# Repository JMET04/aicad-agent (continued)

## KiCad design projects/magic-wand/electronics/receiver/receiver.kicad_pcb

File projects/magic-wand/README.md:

# 魔法杖跨域工程原型包（Rev B）

> **CURRENT 2026-08-23:** Wand 配置保持冻结（几何/布线未变）；BOM 已补全 36/36 LCSC/C-number 并重建制造包，C_HAPTIC_REG/C_HAPTIC_VDD 以 Samsung CL05A105KP5NNNC/C14445 等效替代（X7R→X5R，已记录证据）。独立 receiver-effects 的八槽/八效果 host 逻辑已验证，A1 裸板候选已通过原生 ERC/DRC 并哈希绑定（旧 receiver CAM 仍为 **REJECTED**）。授权仅覆盖原型裸板与原型 3D 打印；PCBA、目标固件、HIL 和量产仍锁定，见 `integration/CURRENT_SYSTEM_STATUS.json`。

当前入口：

- [Current system status](integration/CURRENT_SYSTEM_STATUS.json) — 当前机器可读单一事实源；
- [System engineering handoff](integration/SYSTEM_ENGINEERING_HANDOFF.md) — 接口、开放门和插件升级经验；
- [冻结 Wand 嘉立创裸板包](electronics/manufacturing/jlcpcb-wand-rev-a0/) — 4 层、ERC/DRC 0 的 Wand 裸板上传候选；
- [可打印外壳包](mechanical/printable-wand/) — 含电池位、触觉位、STEP/STL、3D 预览和网格门禁；
- [receiver-effects 系统交接](integration/RECEIVER_EFFECTS_SYSTEM_HANDOFF.md) — 直接 BLE 端点、八槽/八效果、屏幕/音效和开放硬件门；
- [receiver-effects KiCad 工作源](electronics/receiver-effects/) — A1 60 × 50 mm、4 层；ERC/DRC 0/0/0，裸板上传候选已哈希绑定；
- [八类手势主机证据](firmware/gesture-host-evidence.json) — Wand 分类管线证据，不代替目标固件/HIL；
- [接收器运行时主机证据](firmware/host-review-evidence.json) — 34/34 build、10/10 CTest、cppcheck 9/9、52/52 哈希；目标/HIL 仍开放；
- [系统合同与 QA](integration/system-design-contract.json) — 跨域接口、证据和放行锁；
- [当前 SYS-001..012 追踪](integration/current-system-traceability.json) — Rev B 需求到当前合同、门禁和证据的机器映射；
- [当前交付哈希清单](integration/current-delivery-manifest.json) — 当前状态、合同、双交接和五项工具证据的精确闭包；
- [历史机械/电子/整合包](integration/README.md) — Rev A 追溯材料，不再是当前状态源；
- [整机审查 SVG](integration/system-review-overview.svg)；
- [成本粗算](integration/rough-cost-estimate.md)；
- [合并 BOM](integration/combined-bom.csv)。

在仓库根目录复核当前机械与系统门禁：

```powershell
python projects\magic-wand\mechanical\printable-wand\build_printable_wand.py
python plugins\aicad-agent\tests\test_system_engineering_contract.py -v
```

旧的 `integration/build_package.py` 只复现 Rev A 历史快照，不能生成当前状态。

Current authorization is limited to prototype bare-PCB fabrication and prototype 3D printing. The frozen Wand package is already a verified upload candidate; receiver-effects A1 is now also a verified bare-PCB upload candidate (ERC/DRC 0/0/0, hash-bound JLC archive; NINA In1 GND coverage 96% vs the 98% production target remains the only open manufacturing item). PCBA, target-firmware, HIL, production and safety-critical release locks remain closed.

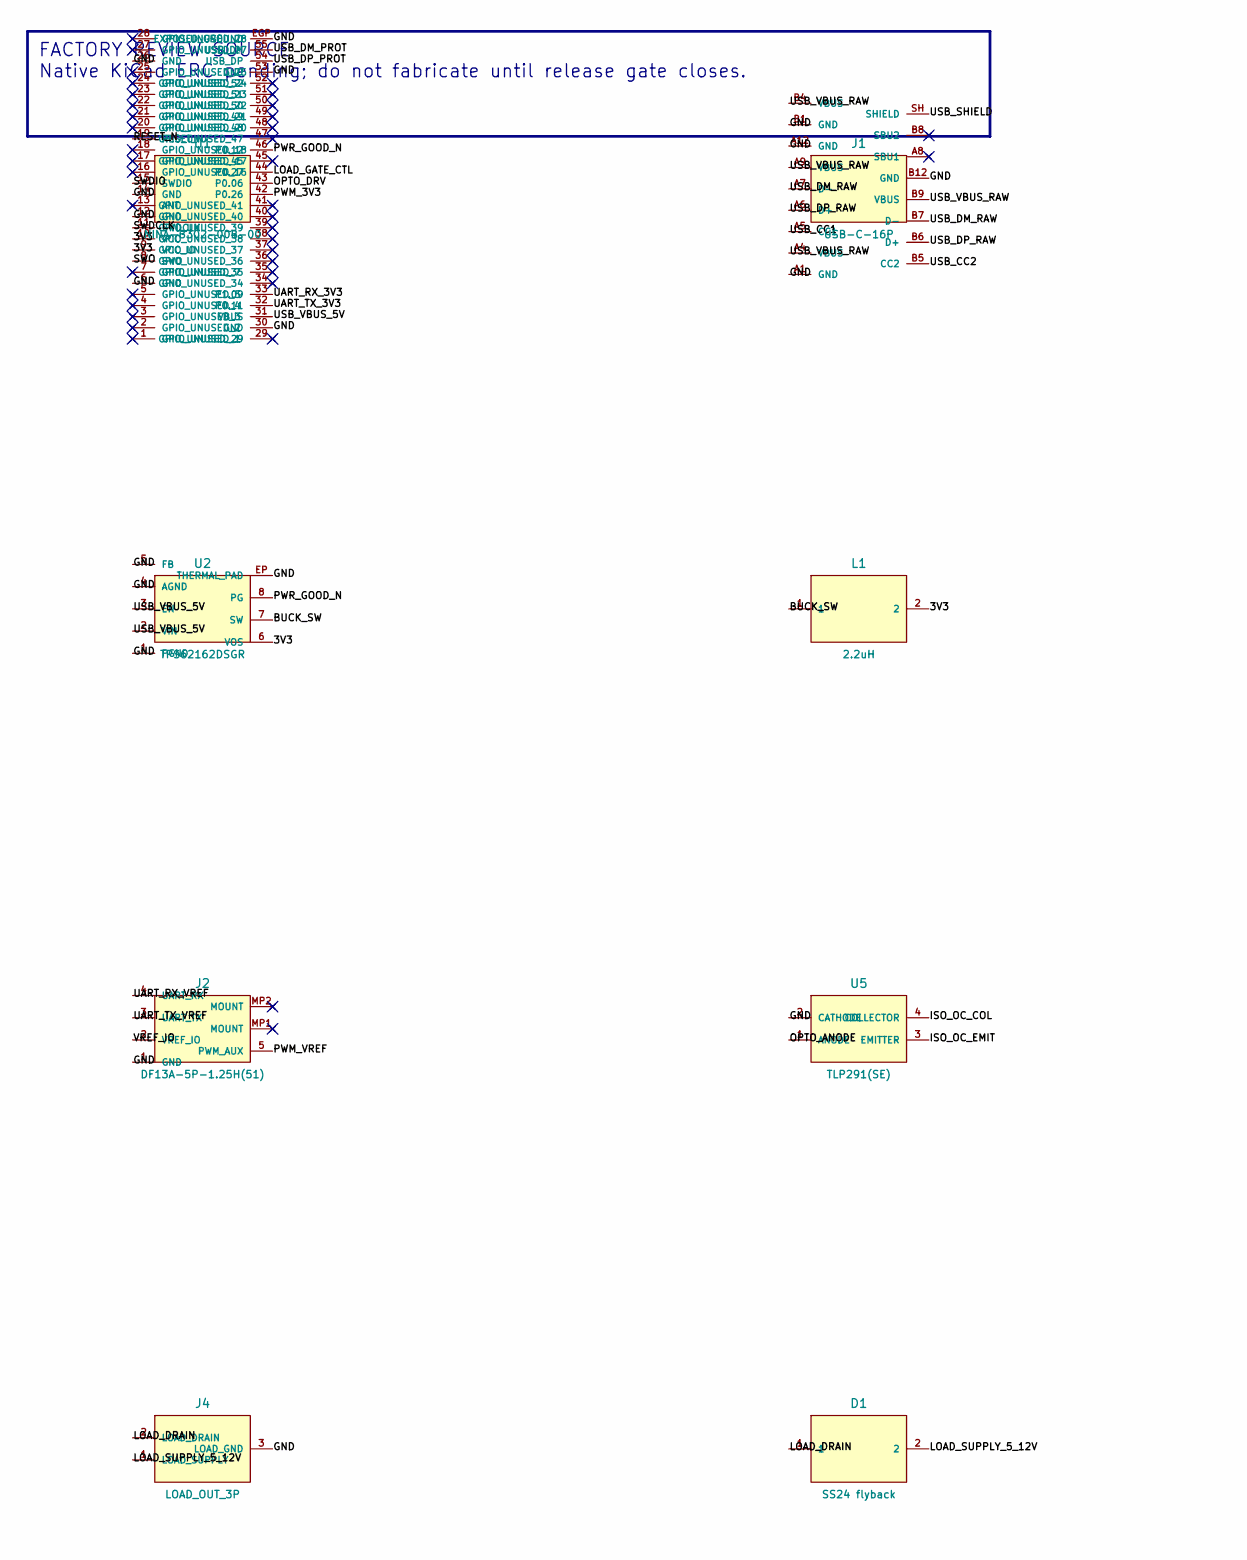
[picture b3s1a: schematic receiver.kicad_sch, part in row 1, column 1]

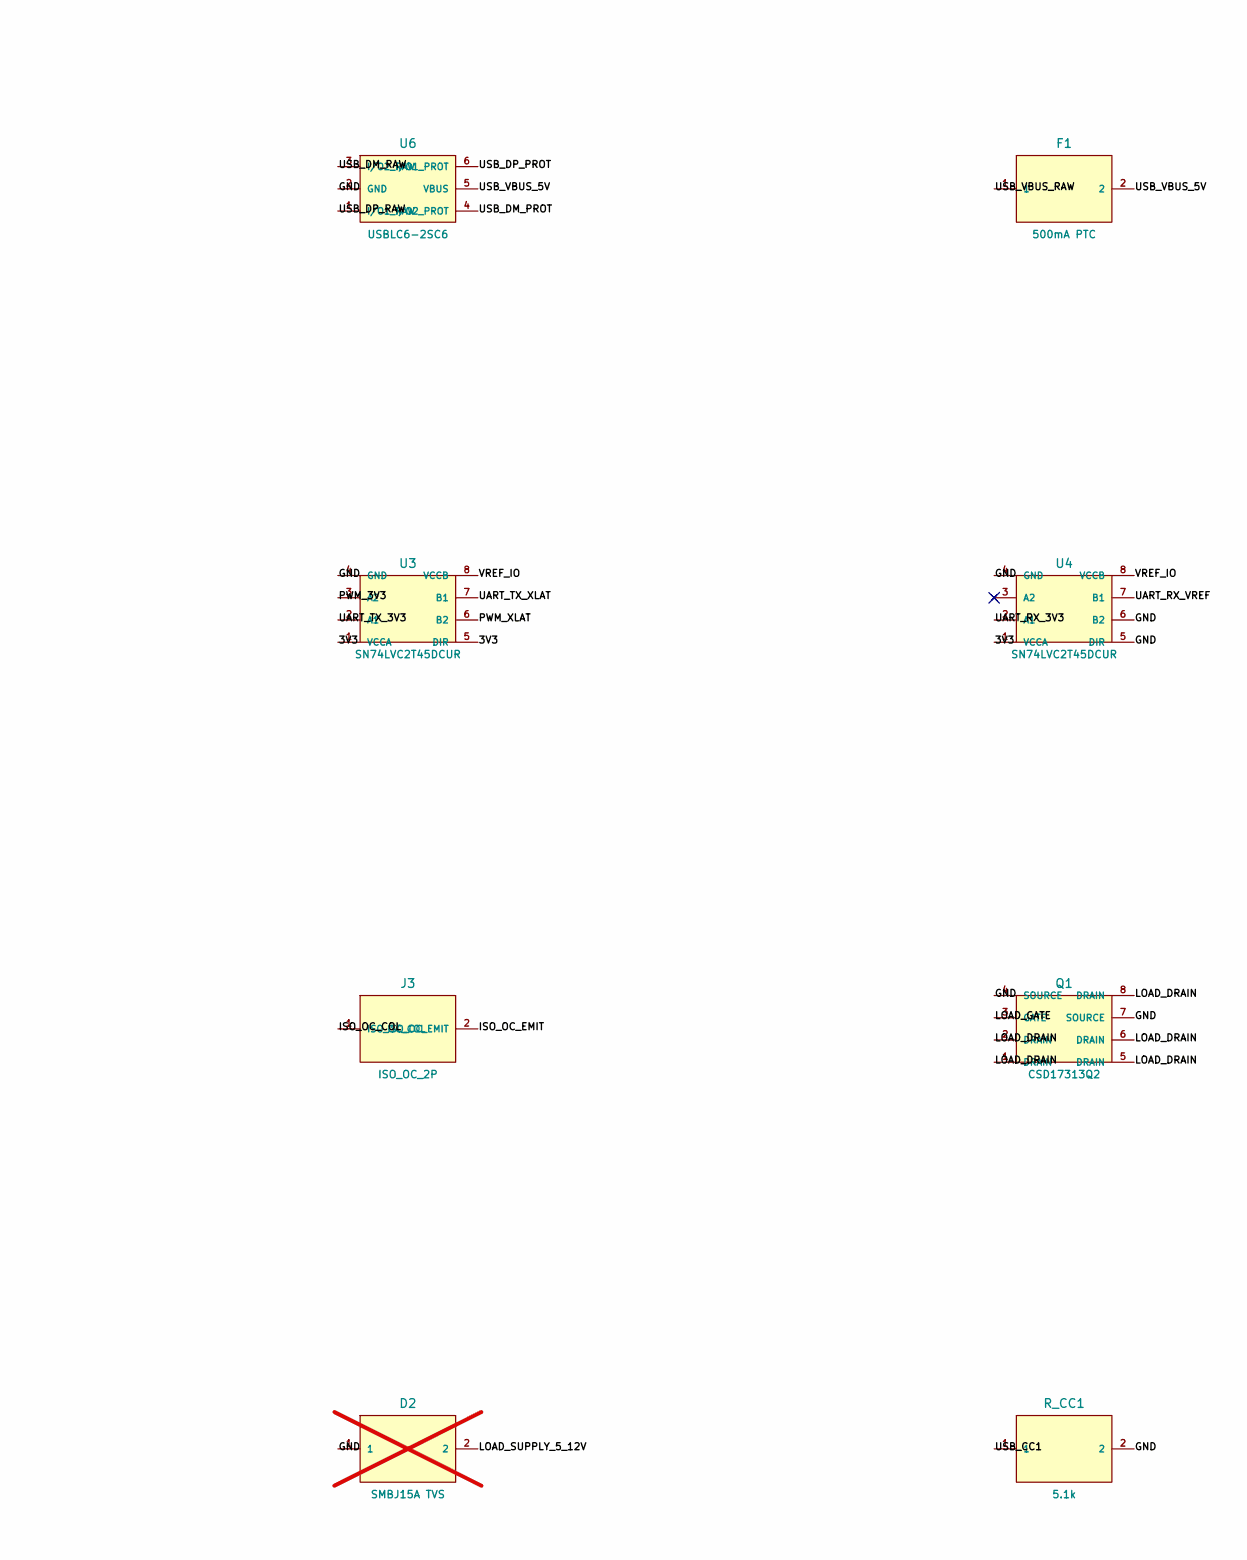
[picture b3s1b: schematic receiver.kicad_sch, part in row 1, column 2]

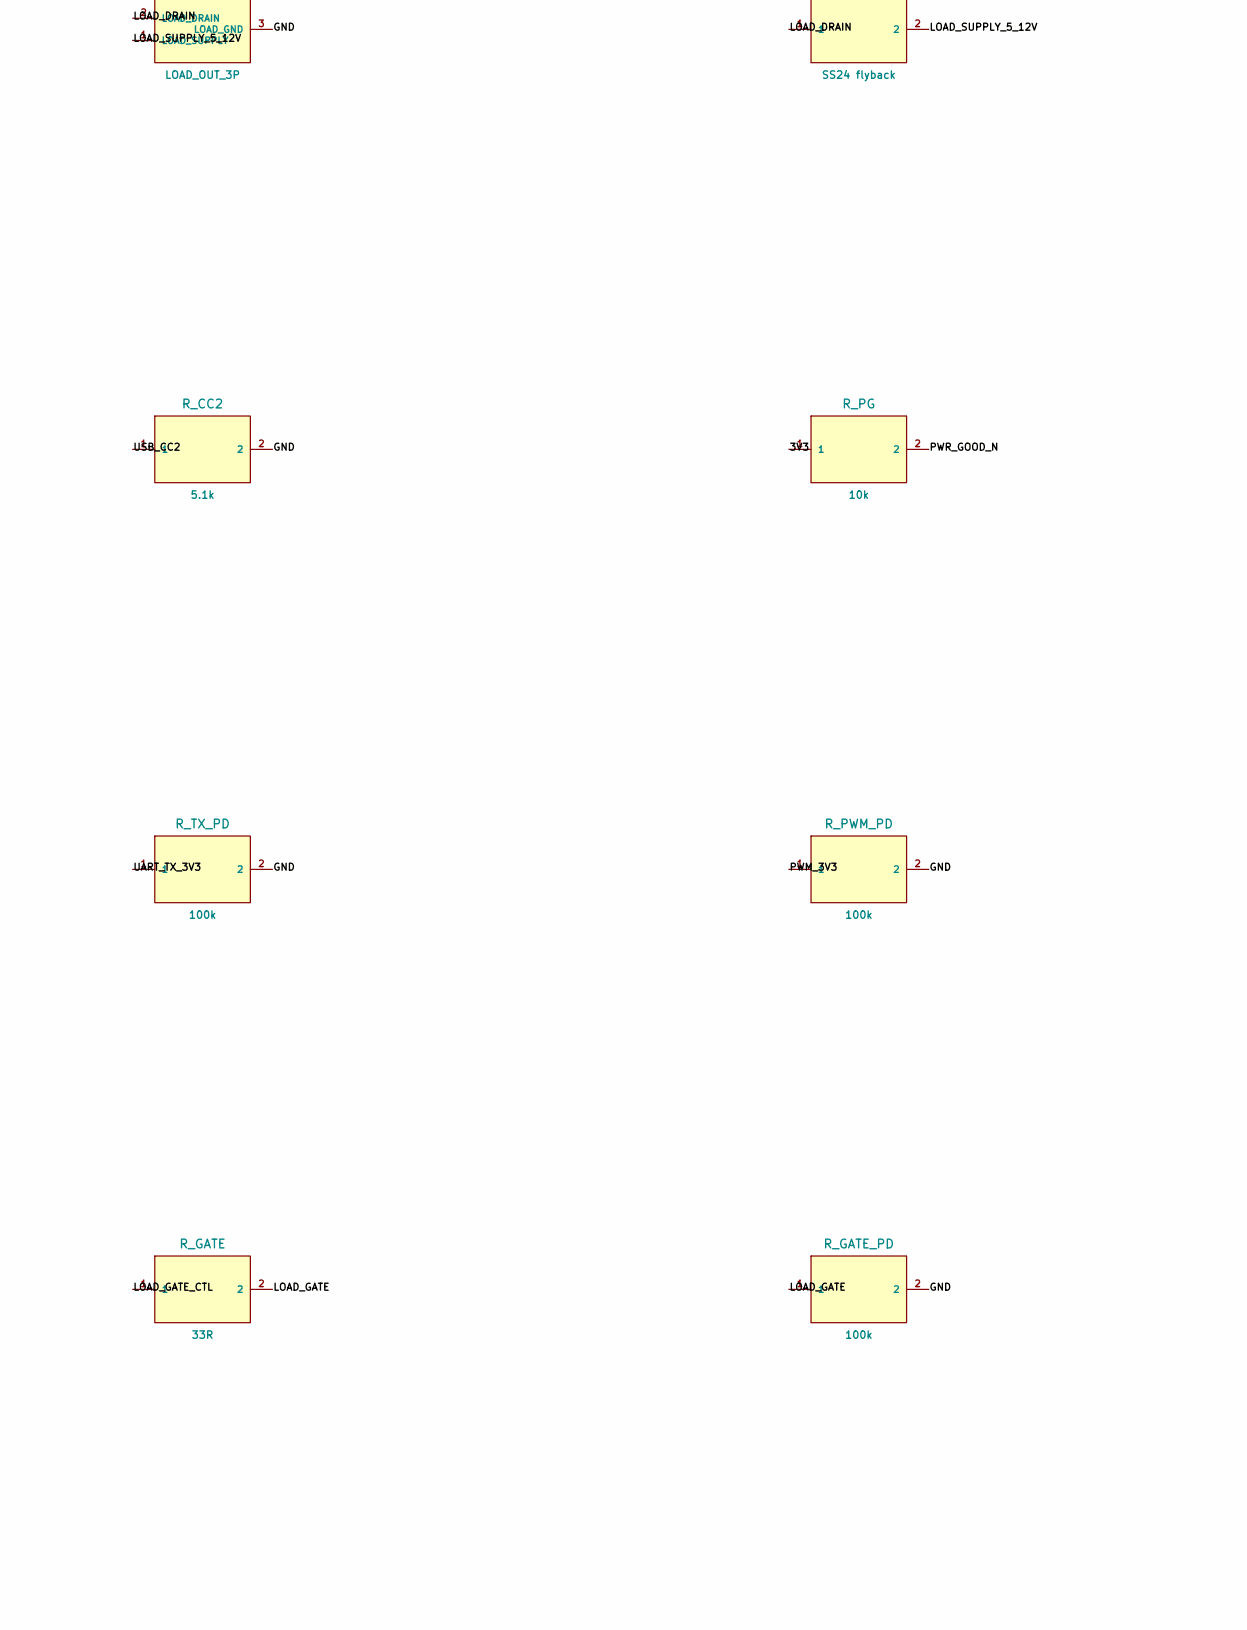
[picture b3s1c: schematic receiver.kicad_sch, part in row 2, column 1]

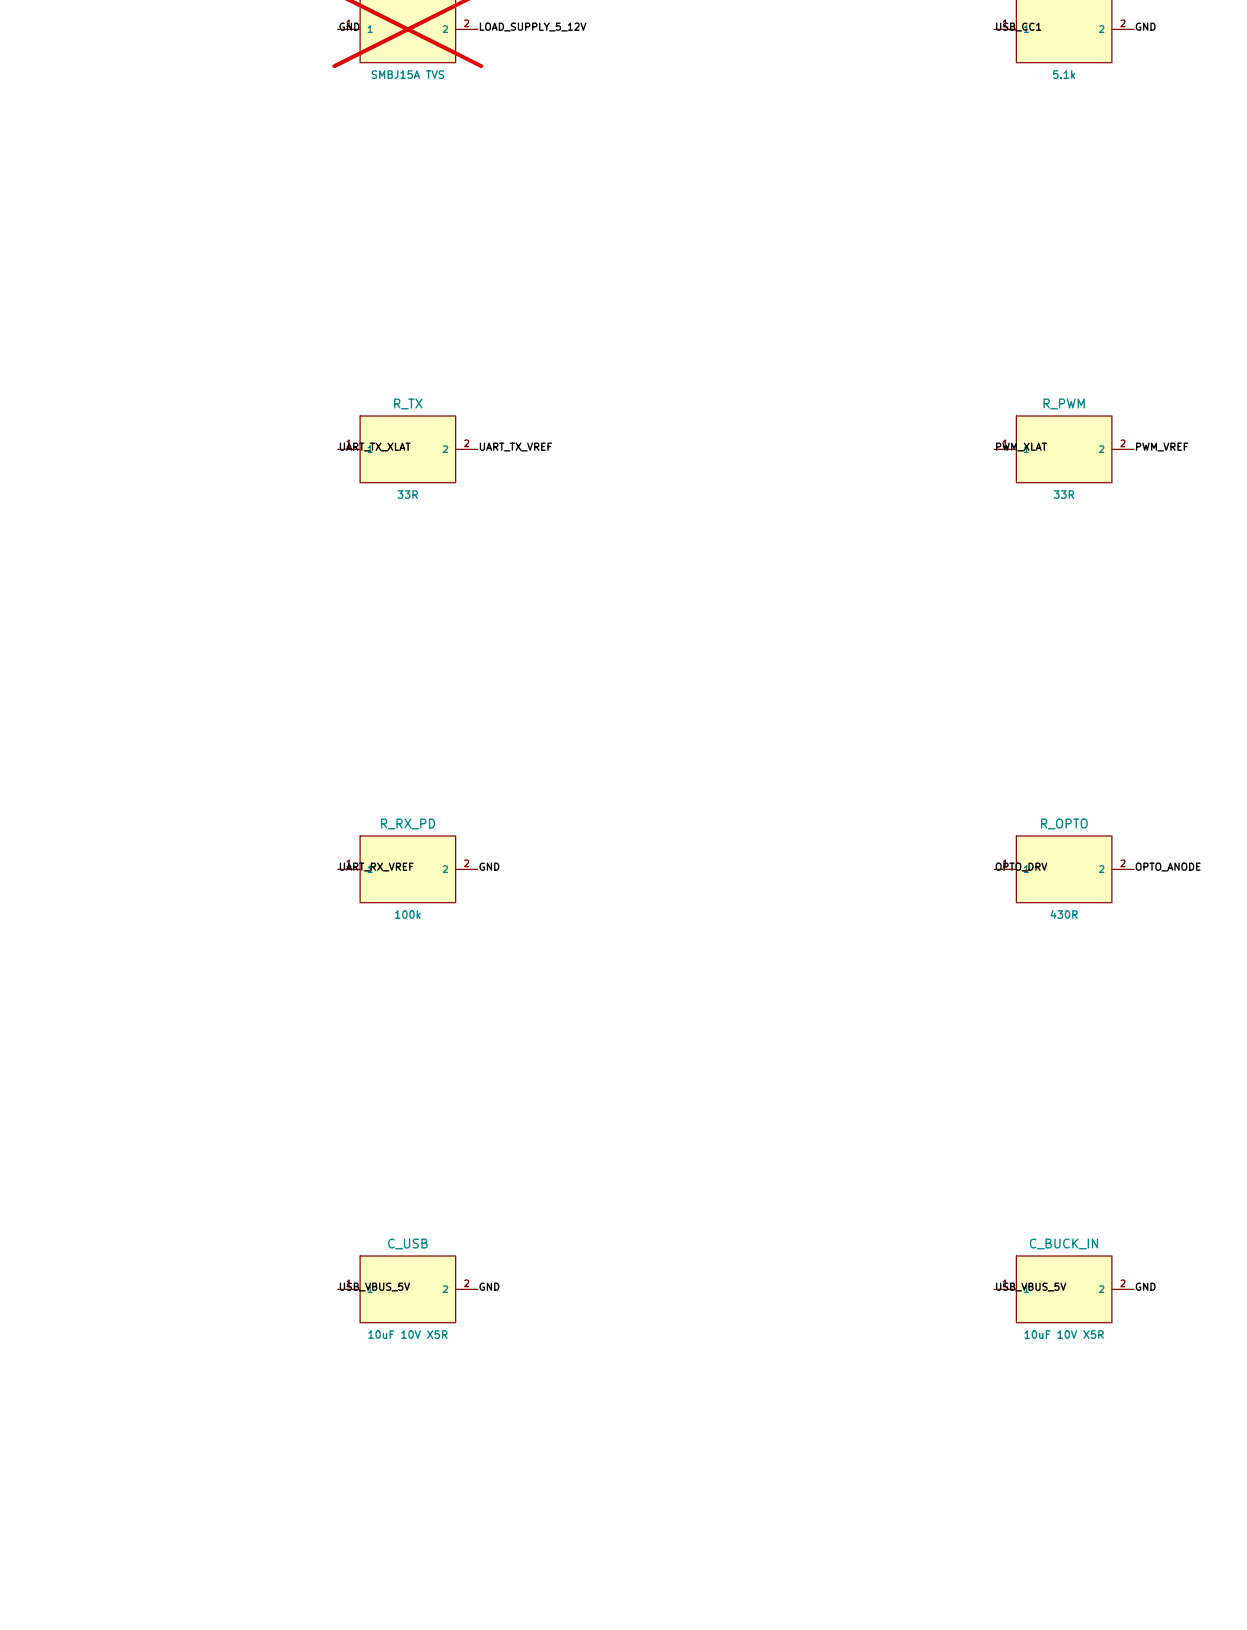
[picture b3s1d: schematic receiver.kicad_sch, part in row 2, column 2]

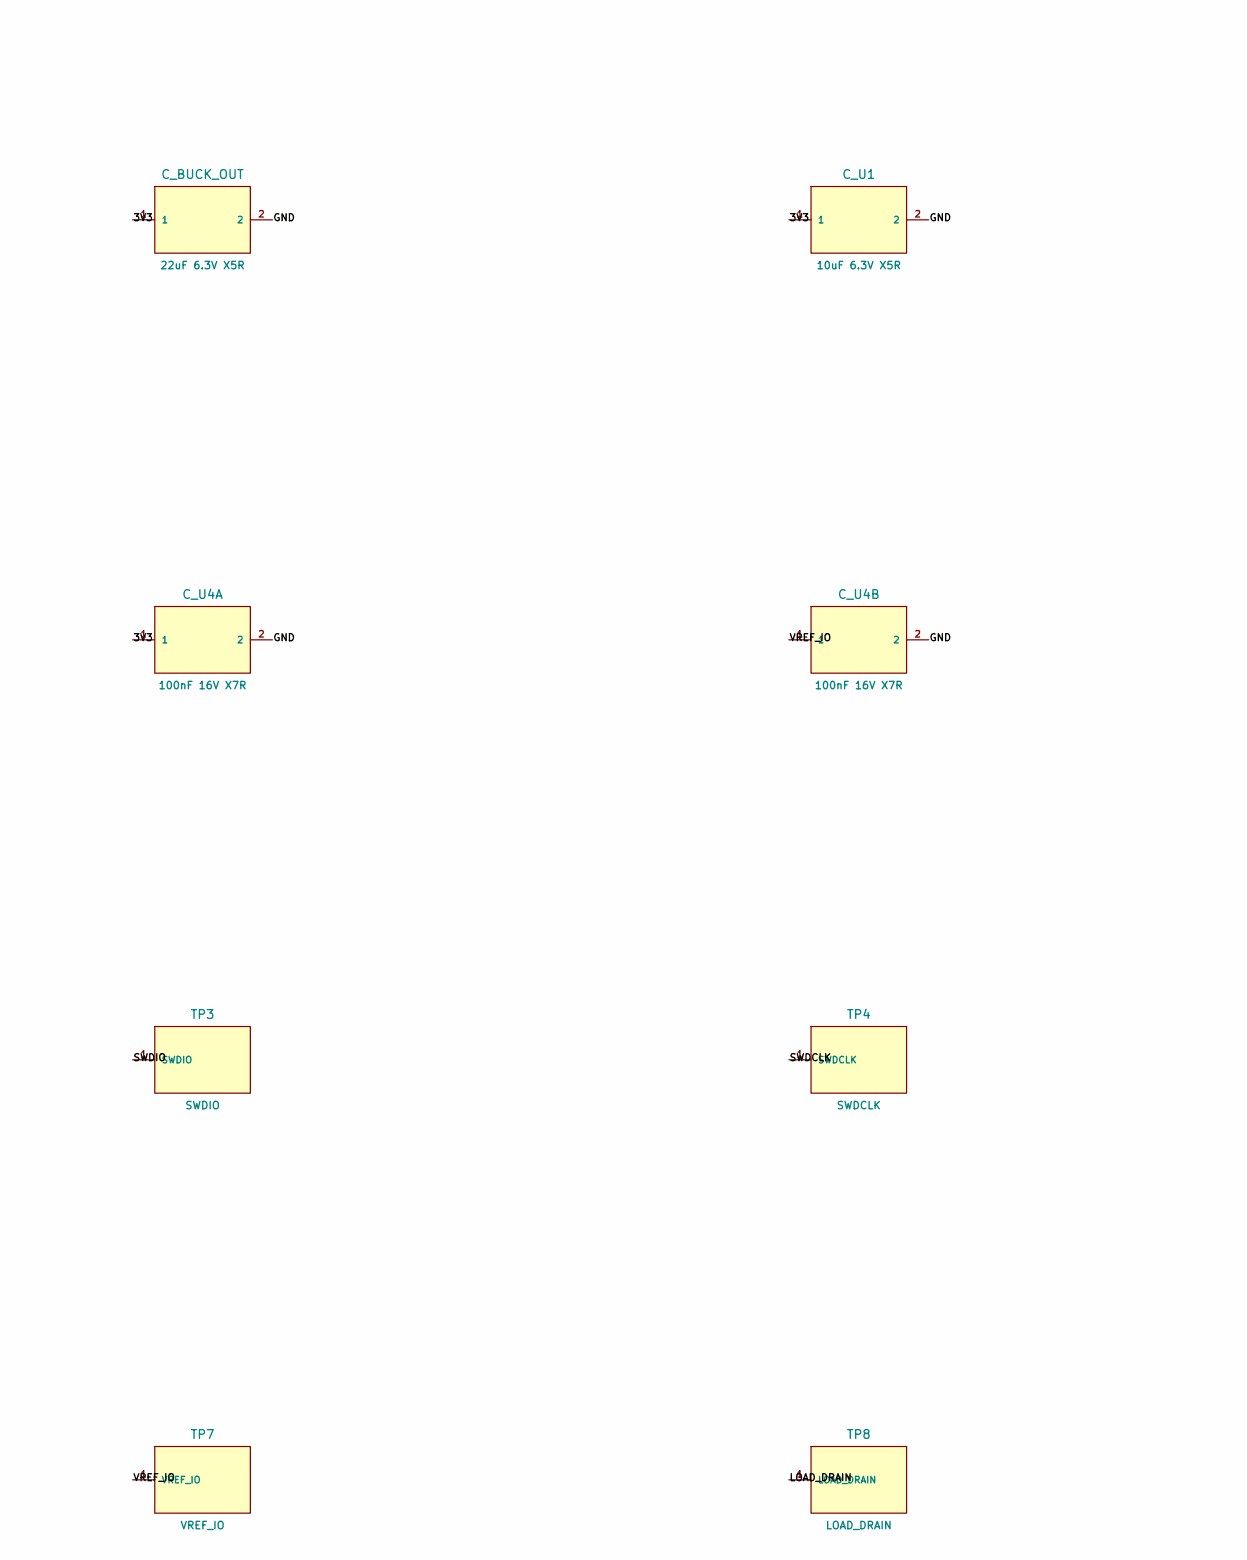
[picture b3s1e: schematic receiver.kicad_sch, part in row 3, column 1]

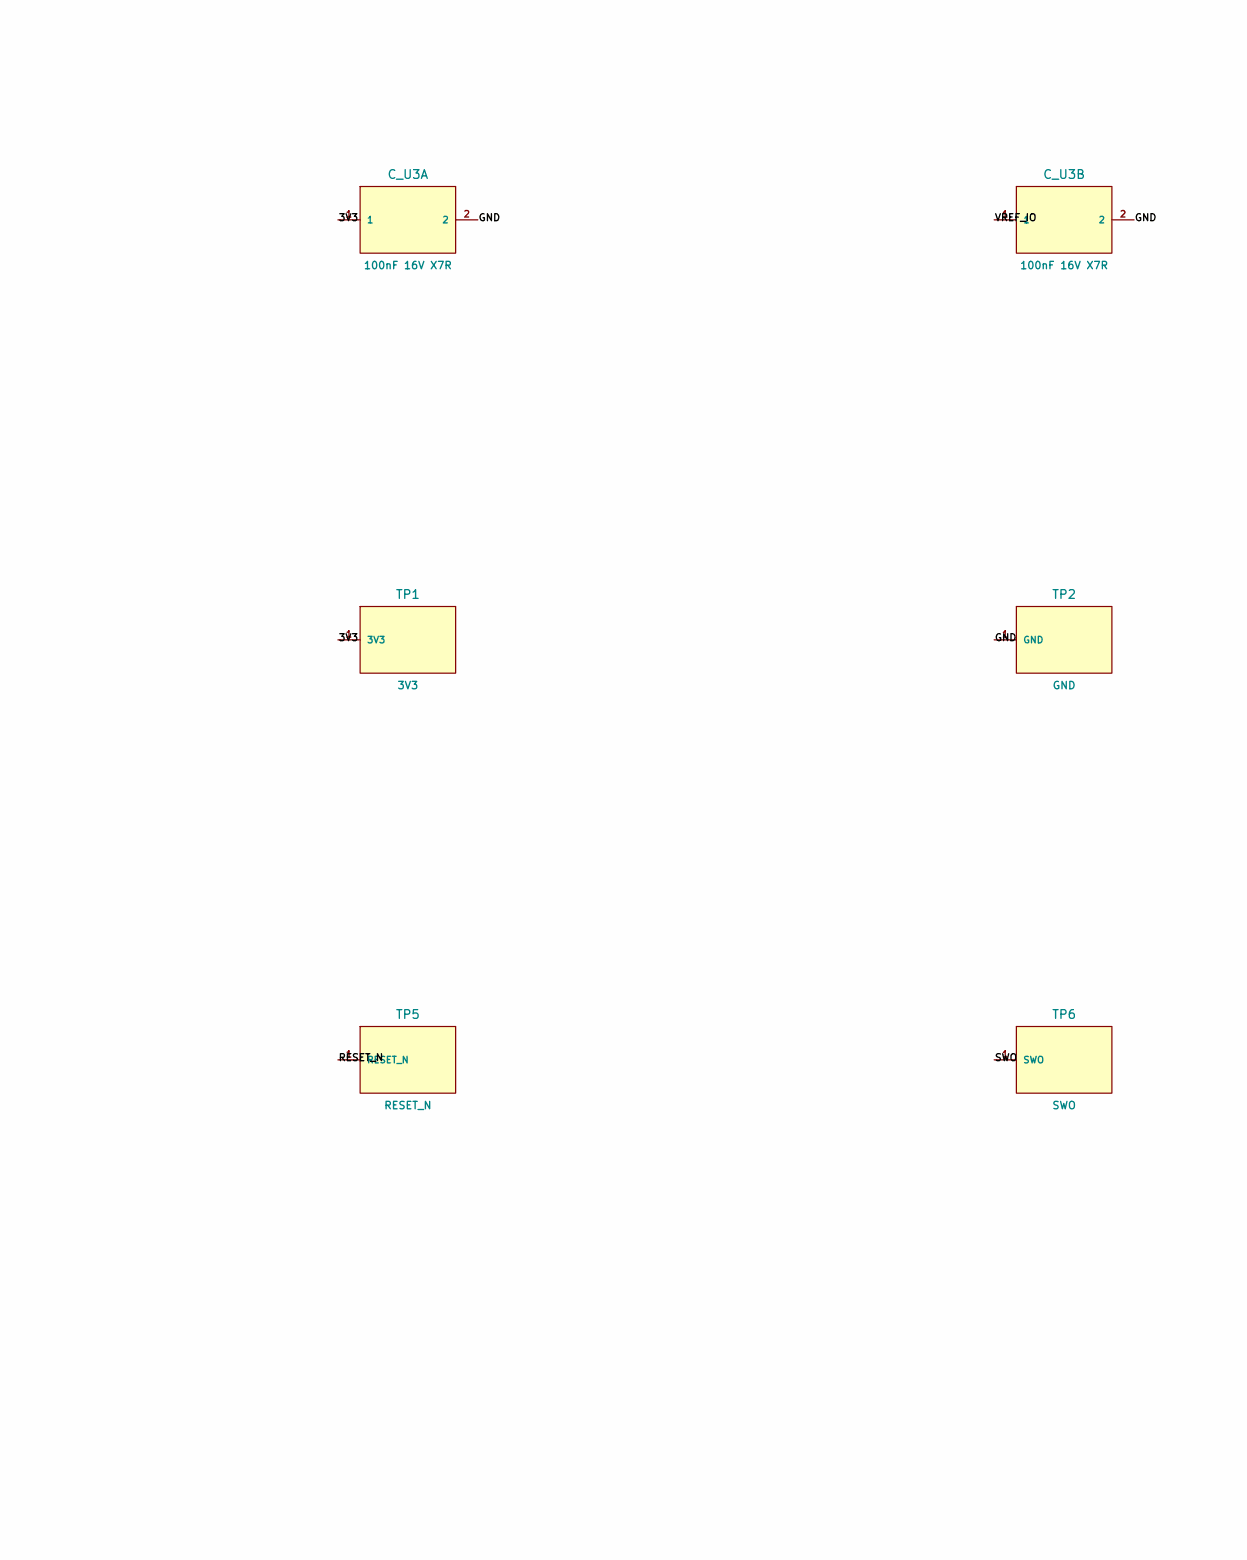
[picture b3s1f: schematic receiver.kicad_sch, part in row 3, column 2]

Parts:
C_BUCK_IN: 10uF 10V X5R; receiver_C_BUCK_IN; MPN GRM21BR61A106KE19L
C_BUCK_OUT: 22uF 6.3V X5R; receiver_C_BUCK_OUT; MPN GRM21BR60J226ME39L
C_U1: 10uF 6.3V X5R; receiver_C_U1; MPN GRM21BR60J106KE19L
C_U3A: 100nF 16V X7R; receiver_C_U3A; MPN GRM155R71C104KA88D
C_U3B: 100nF 16V X7R; receiver_C_U3B; MPN GRM155R71C104KA88D
C_U4A: 100nF 16V X7R; receiver_C_U4A; MPN GRM155R71C104KA88D
C_U4B: 100nF 16V X7R; receiver_C_U4B; MPN GRM155R71C104KA88D
C_USB: 10uF 10V X5R; receiver_C_USB; MPN GRM21BR61A106KE19L
D1: SS24 flyback; receiver_D1; MPN SS24-13-F
D2: SMBJ15A TVS; receiver_D2; MPN SMBJ15A; not fitted
F1: 500mA PTC; receiver_F1; MPN MF-FSMF050X-2
J1: USB-C-16P; receiver_J1; MPN DX07S016JA1R1500
J2: DF13A-5P-1.25H(51); receiver_J2; MPN DF13A-5P-1.25H(51)
J3: ISO_OC_2P; receiver_J3; MPN 282834-2
J4: LOAD_OUT_3P; receiver_J4; MPN 282834-3
L1: 2.2uH; receiver_L1; MPN LQH32PN2R2NN0L
Q1: CSD17313Q2; receiver_Q1; MPN CSD17313Q2
R_CC1: 5.1k; receiver_R_CC1; MPN RC0402FR-075K1L
R_CC2: 5.1k; receiver_R_CC2; MPN RC0402FR-075K1L
R_GATE: 33R; receiver_R_GATE; MPN RC0402FR-0733RL
R_GATE_PD: 100k; receiver_R_GATE_PD; MPN RC0402FR-07100KL
R_OPTO: 430R; receiver_R_OPTO; MPN RC0402FR-07430RL
R_PG: 10k; receiver_R_PG; MPN RC0402FR-0710KL
R_PWM: 33R; receiver_R_PWM; MPN RC0402FR-0733RL
R_PWM_PD: 100k; receiver_R_PWM_PD; MPN RC0402FR-07100KL
R_RX_PD: 100k; receiver_R_RX_PD; MPN RC0402FR-07100KL
R_TX: 33R; receiver_R_TX; MPN RC0402FR-0733RL
R_TX_PD: 100k; receiver_R_TX_PD; MPN RC0402FR-07100KL
TP1: 3V3; receiver_TP1; MPN BARE_PAD_D1.5
TP2: GND; receiver_TP2; MPN BARE_PAD_D1.5
TP3: SWDIO; receiver_TP3; MPN BARE_PAD_D1.5
TP4: SWDCLK; receiver_TP4; MPN BARE_PAD_D1.5
TP5: RESET_N; receiver_TP5; MPN BARE_PAD_D1.5
TP6: SWO; receiver_TP6; MPN BARE_PAD_D1.5
TP7: VREF_IO; receiver_TP7; MPN BARE_PAD_D1.5
TP8: LOAD_DRAIN; receiver_TP8; MPN BARE_PAD_D1.5
U1: NINA-B302-00B-00; receiver_U1; MPN NINA-B302-00B-00
U2: TPS62162DSGR; receiver_U2; MPN TPS62162DSGR
U3: SN74LVC2T45DCUR; receiver_U3; MPN SN74LVC2T45DCUR
U4: SN74LVC2T45DCUR; receiver_U4; MPN SN74LVC2T45DCUR
U5: TLP291(SE); receiver_U5; MPN TLP291(GB-TP,SE)
U6: USBLC6-2SC6; receiver_U6; MPN USBLC6-2SC6

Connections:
3V3: C_BUCK_OUT.1, C_U1.1, C_U3A.1, C_U4A.1, L1.2, R_PG.1, TP1.1 (3V3), U1.9 (VCC_IO), U1.10 (VCC), U2.6 (VOS), U3.1 (VCCA), U3.5 (DIR), U4.1 (VCCA)
BUCK_SW: L1.1, U2.7 (SW)
GND: C_BUCK_IN.2, C_BUCK_OUT.2, C_U1.2, C_U3A.2, C_U3B.2, C_U4A.2, C_U4B.2, C_USB.2, D2.1, J1.A1 (GND), J1.A12 (GND), J1.B1 (GND), J1.B12 (GND), J2.1 (GND), J4.3 (LOAD_GND), Q1.4 (SOURCE), Q1.7 (SOURCE), R_CC1.2, R_CC2.2, R_GATE_PD.2, R_PWM_PD.2, R_RX_PD.2, R_TX_PD.2, TP2.1 (GND), U1.6 (GND), U1.12 (GND), U1.14 (GND), U1.26 (GND), U1.30 (GND), U1.53 (GND), U1.EGP (EXPOSED_GROUND), U2.1 (PGND), U2.4 (AGND), U2.5 (FB), U2.EP (THERMAL_PAD), U3.4 (GND), U4.4 (GND), U4.5 (DIR), U4.6 (B2), U5.2 (CATHODE), U6.2 (GND)
ISO_OC_COL: J3.1 (ISO_OC_COL), U5.4 (COLLECTOR)
ISO_OC_EMIT: J3.2 (ISO_OC_EMIT), U5.3 (EMITTER)
LOAD_DRAIN: D1.1, J4.2 (LOAD_DRAIN), Q1.1 (DRAIN), Q1.2 (DRAIN), Q1.5 (DRAIN), Q1.6 (DRAIN), Q1.8 (DRAIN), TP8.1 (LOAD_DRAIN)
LOAD_GATE: Q1.3 (GATE), R_GATE.2, R_GATE_PD.1
LOAD_GATE_CTL: R_GATE.1, U1.44 (P0.27)
LOAD_SUPPLY_5_12V: D1.2, D2.2, J4.1 (LOAD_SUPPLY)
OPTO_ANODE: R_OPTO.2, U5.1 (ANODE)
OPTO_DRV: R_OPTO.1, U1.43 (P0.06)
PWM_3V3: R_PWM_PD.1, U1.42 (P0.26), U3.3 (A2)
PWM_VREF: J2.5 (PWM_AUX), R_PWM.2
PWM_XLAT: R_PWM.1, U3.6 (B2)
PWR_GOOD_N: R_PG.2, U1.46 (P0.12), U2.8 (PG)
RESET_N: TP5.1 (RESET_N), U1.19 (RESET_N)
SWDCLK: TP4.1 (SWDCLK), U1.11 (SWDCLK)
SWDIO: TP3.1 (SWDIO), U1.15 (SWDIO)
SWO: TP6.1 (SWO), U1.8 (SWO)
UART_RX_3V3: U1.33 (P1.09), U4.2 (A1)
UART_RX_VREF: J2.4 (UART_RX), R_RX_PD.1, U4.7 (B1)
UART_TX_3V3: R_TX_PD.1, U1.32 (P0.11), U3.2 (A1)
UART_TX_VREF: J2.3 (UART_TX), R_TX.2
UART_TX_XLAT: R_TX.1, U3.7 (B1)
USB_CC1: J1.A5 (CC1), R_CC1.1
USB_CC2: J1.B5 (CC2), R_CC2.1
USB_DM_PROT: U1.55 (USB_DM), U6.4 (I/O2_PROT)
USB_DM_RAW: J1.A7 (D-), J1.B7 (D-), U6.3 (I/O2_RAW)
USB_DP_PROT: U1.54 (USB_DP), U6.6 (I/O1_PROT)
USB_DP_RAW: J1.A6 (D+), J1.B6 (D+), U6.1 (I/O1_RAW)
USB_SHIELD: J1.SH (SHIELD)
USB_VBUS_5V: C_BUCK_IN.1, C_USB.1, F1.2, U1.31 (VBUS), U2.2 (VIN), U2.3 (EN), U6.5 (VBUS)
USB_VBUS_RAW: F1.1, J1.A4 (VBUS), J1.A9 (VBUS), J1.B4 (VBUS), J1.B9 (VBUS)
VREF_IO: C_U3B.1, C_U4B.1, J2.2 (VREF_IO), TP7.1 (VREF_IO), U3.8 (VCCB), U4.8 (VCCB)

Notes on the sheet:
FACTORY REVIEW SOURCE Native KiCad ERC pending; do not fabricate until release gate closes.

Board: 4 copper layers, 46 parts (0 on the bottom side), 33 nets, no tracks yet.

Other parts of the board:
H1: MountingHole_2.4mm; receiver_H1
H2: MountingHole_2.4mm; receiver_H2
H3: MountingHole_2.4mm; receiver_H3
H4: MountingHole_2.4mm; receiver_H4
